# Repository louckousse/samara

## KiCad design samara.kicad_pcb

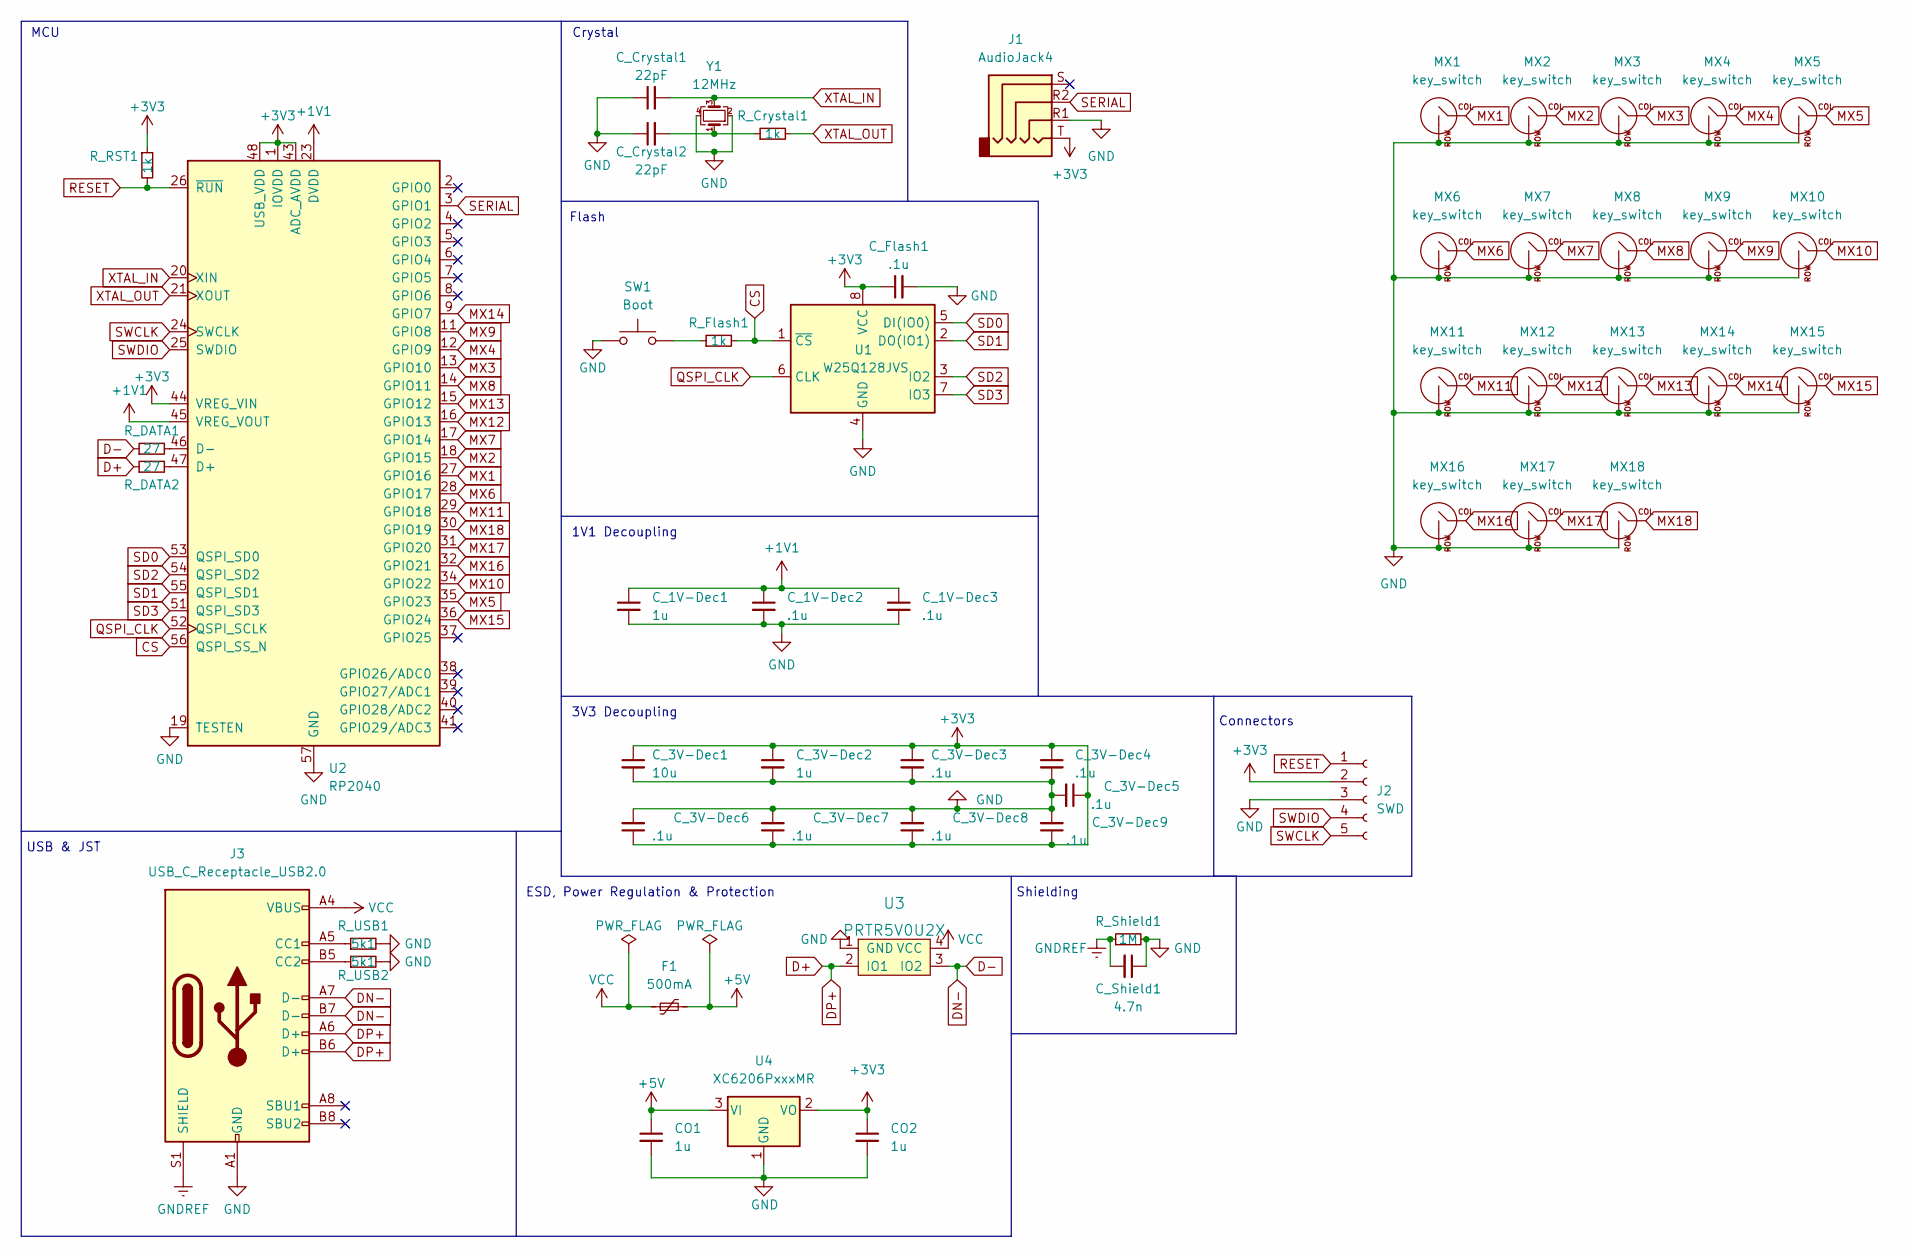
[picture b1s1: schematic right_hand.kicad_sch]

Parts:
CO1, CO2: 1u; C_0402_1005Metric
C_1V-Dec1, C_3V-Dec2: 1u; C_0402_1005Metric
C_1V-Dec2, C_1V-Dec3, C_3V-Dec3, C_3V-Dec4, C_3V-Dec5, C_3V-Dec6, C_3V-Dec7, C_3V-Dec8, C_3V-Dec9: .1u; C_0402_1005Metric
C_3V-Dec1: 10u; C_0402_1005Metric
C_Crystal1, C_Crystal2: 22pF; C_0402_1005Metric
C_Flash1: .1u; C_0402_1005Metric
C_Shield1: 4.7n; C_0402_1005Metric
F1: 500mA; Fuse_0805_2012Metric
J1: AudioJack4; Jack_3.5mm_PJ320D_Horizontal
J2: SWD; PinHeader_1x05_P2.54mm_Vertical
J3: USB_C_Receptacle_USB2.0; HRO-TYPE-C-31-M-12-Assembly
MX1, MX2, MX3, MX4, MX5, MX6, MX7, MX8, MX9, MX10, MX11, MX12, MX13, MX14, MX15, MX16, MX17, MX18: key_switch; Kailh_socket_MX
R_Crystal1: 1k; R_0402_1005Metric
R_DATA1, R_DATA2: 27; R_0402_1005Metric
R_Flash1: 1k; R_0402_1005Metric
R_RST1: 1k; R_0402_1005Metric
R_Shield1: 1M; R_0402_1005Metric
R_USB1, R_USB2: 5k1; R_0402_1005Metric
SW1: Boot; PinHeader_1x02_P2.54mm_Vertical
U1: W25Q128JVS; SOIC-8_5.23x5.23mm_P1.27mm
U2: RP2040; RP2040-QFN-56
U3: PRTR5V0U2X; SOT-143
U4: XC6206PxxxMR; SOT-23
Y1: 12MHz; Crystal_SMD_3225-4Pin_3.2x2.5mm

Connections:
+1V1: C_1V-Dec1.1, C_1V-Dec2.1, C_1V-Dec3.1, U2.23 (DVDD), U2.45 (VREG_VOUT), U2.50 (DVDD); also elsewhere on the board
+3V3: CO2.1, C_3V-Dec1.1, C_3V-Dec2.1, C_3V-Dec3.1, C_3V-Dec4.1, C_3V-Dec5.1, C_3V-Dec6.1, C_3V-Dec7.1, C_3V-Dec8.1, C_3V-Dec9.1, C_Flash1.1, J1.T, J2.2, R_RST1.1, U1.8 (VCC), U2.1 (IOVDD), U2.10 (IOVDD), U2.22 (IOVDD), U2.33 (IOVDD), U2.42 (IOVDD), U2.43 (ADC_AVDD), U2.44 (VREG_VIN), U2.48 (USB_VDD), U2.49 (IOVDD), U4.2 (VO); also elsewhere on the board
+5V: CO1.1, F1.2, U4.3 (VI); also elsewhere on the board
CS: R_Flash1.2, U1.1 (~CS), U2.56 (QSPI_SS_N)
D+: J3.A6 (D+), J3.B6 (D+), R_DATA2.1, U3.2 (IO1)
D-: J3.A7 (D-), J3.B7 (D-), R_DATA1.1, U3.3 (IO2)
GND: CO1.2, CO2.2, C_1V-Dec1.2, C_1V-Dec2.2, C_1V-Dec3.2, C_3V-Dec1.2, C_3V-Dec2.2, C_3V-Dec3.2, C_3V-Dec4.2, C_3V-Dec5.2, C_3V-Dec6.2, C_3V-Dec7.2, C_3V-Dec8.2, C_3V-Dec9.2, C_Crystal1.1, C_Crystal2.1, C_Flash1.2, C_Shield1.1, J1.R1, J2.3, J3.A1 (GND), J3.B1 (GND), MX1.2 (ROW), MX2.2 (ROW), MX3.2 (ROW), MX4.2 (ROW), MX5.2 (ROW), MX6.2 (ROW), MX7.2 (ROW), MX8.2 (ROW), MX9.2 (ROW), MX10.2 (ROW), MX11.2 (ROW), MX12.2 (ROW), MX13.2 (ROW), MX14.2 (ROW), MX15.2 (ROW), MX16.2 (ROW), MX17.2 (ROW), MX18.2 (ROW), R_Shield1.2, R_USB1.2, R_USB2.2, SW1.1, U1.4 (GND), U2.19 (TESTEN), U2.57 (GND), U3.1 (GND), U4.1 (GND), Y1.2, Y1.4; also elsewhere on the board
GNDREF: C_Shield1.2, J3.S1 (SHIELD), R_Shield1.1; also elsewhere on the board
MX1: MX1.1 (Passive), U2.27 (GPIO16)
MX2: MX2.1 (Passive), U2.18 (GPIO15)
MX3: MX3.1 (Passive), U2.13 (GPIO10)
MX4: MX4.1 (Passive), U2.12 (GPIO9)
MX5: MX5.1 (Passive), U2.35 (GPIO23)
MX6: MX6.1 (Passive), U2.28 (GPIO17)
MX7: MX7.1 (Passive), U2.17 (GPIO14)
MX8: MX8.1 (Passive), U2.14 (GPIO11)
MX9: MX9.1 (Passive), U2.11 (GPIO8)
MX10: MX10.1 (Passive), U2.34 (GPIO22)
MX11: MX11.1 (Passive), U2.29 (GPIO18)
MX12: MX12.1 (Passive), U2.16 (GPIO13)
MX13: MX13.1 (Passive), U2.15 (GPIO12)
MX14: MX14.1 (Passive), U2.9 (GPIO7)
MX15: MX15.1 (Passive), U2.36 (GPIO24)
MX16: MX16.1 (Passive), U2.32 (GPIO21)
MX17: MX17.1 (Passive), U2.31 (GPIO20)
MX18: MX18.1 (Passive), U2.30 (GPIO19)
unnamed: C_Crystal2.2, R_Crystal1.1, Y1.1
unnamed: J3.A5 (CC1), R_USB1.1
unnamed: J3.B5 (CC2), R_USB2.1
unnamed: R_Flash1.1, SW1.2
unnamed: R_DATA2.2, U2.47 (D+)
unnamed: R_DATA1.2, U2.46 (D-)
QSPI_CLK: U1.6 (CLK), U2.52 (QSPI_SCLK)
RESET: J2.1, R_RST1.2, U2.26 (~RUN)
SD0: U1.5 (DI(IO0)), U2.53 (QSPI_SD0)
SD1: U1.2 (DO(IO1)), U2.55 (QSPI_SD1)
SD2: U1.3 (IO2), U2.54 (QSPI_SD2)
SD3: U1.7 (IO3), U2.51 (QSPI_SD3)
SERIAL: J1.R2, U2.3 (GPIO1)
SWCLK: J2.5, U2.24 (SWCLK)
SWDIO: J2.4, U2.25 (SWDIO)
VCC: F1.1, J3.A4 (VBUS), J3.B4 (VBUS), U3.4 (VCC); also elsewhere on the board
XTAL_IN: C_Crystal1.2, U2.20 (XIN), Y1.3
XTAL_OUT: R_Crystal1.2, U2.21 (XOUT)

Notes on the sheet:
USB & JST
MCU
Connectors
3V3 Decoupling
ESD, Power Regulation & Protection
Shielding
Flash
Crystal
1V1 Decoupling

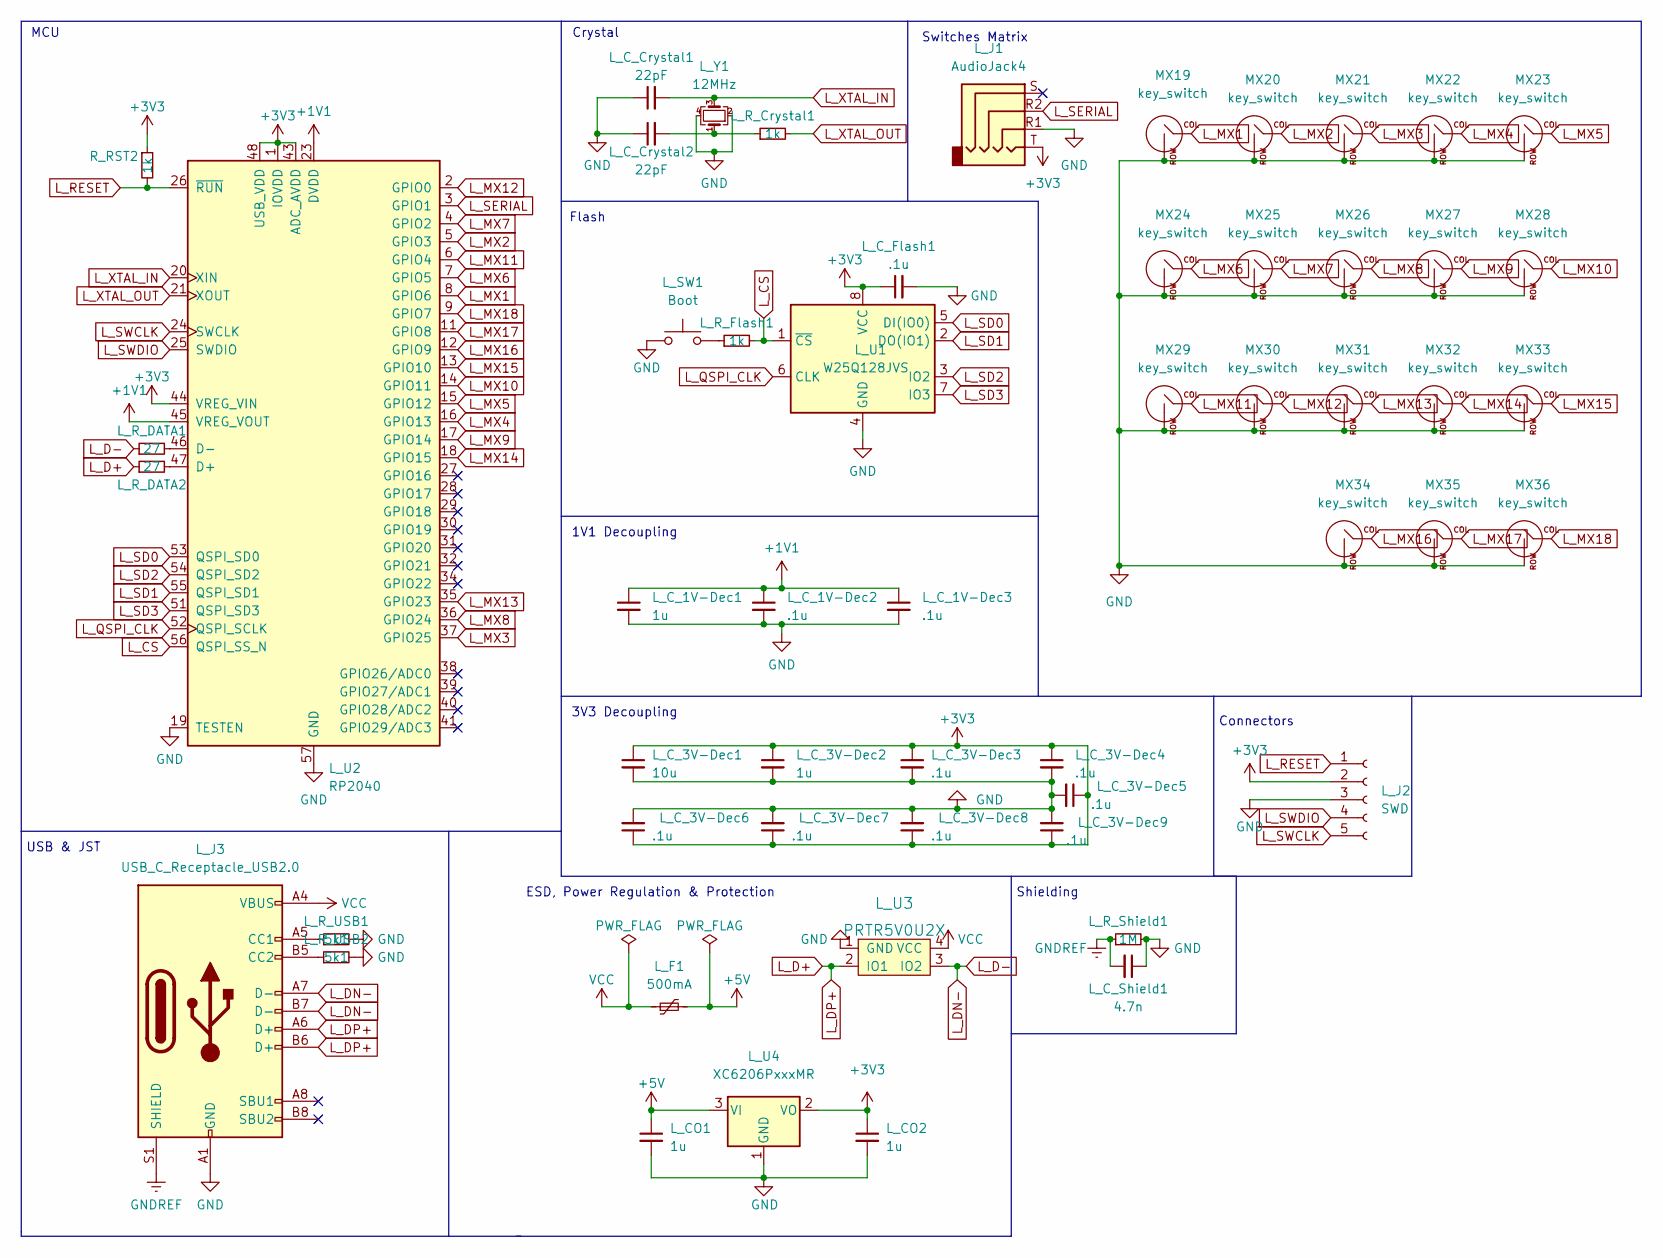
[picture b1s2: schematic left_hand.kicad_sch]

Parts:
L_CO1, L_CO2: 1u; C_0402_1005Metric
L_C_1V-Dec1, L_C_3V-Dec2: 1u; C_0402_1005Metric
L_C_1V-Dec2, L_C_1V-Dec3, L_C_3V-Dec3, L_C_3V-Dec4, L_C_3V-Dec5, L_C_3V-Dec6, L_C_3V-Dec7, L_C_3V-Dec8, L_C_3V-Dec9: .1u; C_0402_1005Metric
L_C_3V-Dec1: 10u; C_0402_1005Metric
L_C_Crystal1, L_C_Crystal2: 22pF; C_0402_1005Metric
L_C_Flash1: .1u; C_0402_1005Metric
L_C_Shield1: 4.7n; C_0402_1005Metric
L_F1: 500mA; Fuse_0805_2012Metric
L_J1: AudioJack4; Jack_3.5mm_PJ320D_Horizontal
L_J2: SWD; PinHeader_1x05_P2.54mm_Vertical
L_J3: USB_C_Receptacle_USB2.0; HRO-TYPE-C-31-M-12-Assembly
L_R_Crystal1: 1k; R_0402_1005Metric
L_R_DATA1, L_R_DATA2: 27; R_0402_1005Metric
L_R_Flash1: 1k; R_0402_1005Metric
L_R_Shield1: 1M; R_0402_1005Metric
L_R_USB1, L_R_USB2: 5k1; R_0402_1005Metric
L_SW1: Boot; PinHeader_1x02_P2.54mm_Vertical
L_U1: W25Q128JVS; SOIC-8_5.23x5.23mm_P1.27mm
L_U2: RP2040; RP2040-QFN-56
L_U3: PRTR5V0U2X; SOT-143
L_U4: XC6206PxxxMR; SOT-23
L_Y1: 12MHz; Crystal_SMD_3225-4Pin_3.2x2.5mm
MX19, MX20, MX21, MX22, MX23, MX24, MX25, MX26, MX27, MX28, MX29, MX30, MX31, MX32, MX33, MX34, MX35, MX36: key_switch; Kailh_socket_MX
R_RST2: 1k; R_0402_1005Metric

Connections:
+1V1: L_C_1V-Dec1.1, L_C_1V-Dec2.1, L_C_1V-Dec3.1, L_U2.23 (DVDD), L_U2.45 (VREG_VOUT), L_U2.50 (DVDD); also elsewhere on the board
+3V3: L_CO2.1, L_C_3V-Dec1.1, L_C_3V-Dec2.1, L_C_3V-Dec3.1, L_C_3V-Dec4.1, L_C_3V-Dec5.1, L_C_3V-Dec6.1, L_C_3V-Dec7.1, L_C_3V-Dec8.1, L_C_3V-Dec9.1, L_C_Flash1.1, L_J1.T, L_J2.2, L_U1.8 (VCC), L_U2.1 (IOVDD), L_U2.10 (IOVDD), L_U2.22 (IOVDD), L_U2.33 (IOVDD), L_U2.42 (IOVDD), L_U2.43 (ADC_AVDD), L_U2.44 (VREG_VIN), L_U2.48 (USB_VDD), L_U2.49 (IOVDD), L_U4.2 (VO), R_RST2.1; also elsewhere on the board
+5V: L_CO1.1, L_F1.2, L_U4.3 (VI); also elsewhere on the board
GND: L_CO1.2, L_CO2.2, L_C_1V-Dec1.2, L_C_1V-Dec2.2, L_C_1V-Dec3.2, L_C_3V-Dec1.2, L_C_3V-Dec2.2, L_C_3V-Dec3.2, L_C_3V-Dec4.2, L_C_3V-Dec5.2, L_C_3V-Dec6.2, L_C_3V-Dec7.2, L_C_3V-Dec8.2, L_C_3V-Dec9.2, L_C_Crystal1.1, L_C_Crystal2.1, L_C_Flash1.2, L_C_Shield1.1, L_J1.R1, L_J2.3, L_J3.A1 (GND), L_J3.B1 (GND), L_R_Shield1.2, L_R_USB1.2, L_R_USB2.2, L_SW1.1, L_U1.4 (GND), L_U2.19 (TESTEN), L_U2.57 (GND), L_U3.1 (GND), L_U4.1 (GND), L_Y1.2, L_Y1.4, MX19.2 (ROW), MX20.2 (ROW), MX21.2 (ROW), MX22.2 (ROW), MX23.2 (ROW), MX24.2 (ROW), MX25.2 (ROW), MX26.2 (ROW), MX27.2 (ROW), MX28.2 (ROW), MX29.2 (ROW), MX30.2 (ROW), MX31.2 (ROW), MX32.2 (ROW), MX33.2 (ROW), MX34.2 (ROW), MX35.2 (ROW), MX36.2 (ROW); also elsewhere on the board
GNDREF: L_C_Shield1.2, L_J3.S1 (SHIELD), L_R_Shield1.1; also elsewhere on the board
L_CS: L_R_Flash1.2, L_U1.1 (~CS), L_U2.56 (QSPI_SS_N)
L_D+: L_J3.A6 (D+), L_J3.B6 (D+), L_R_DATA2.1, L_U3.2 (IO1)
L_D-: L_J3.A7 (D-), L_J3.B7 (D-), L_R_DATA1.1, L_U3.3 (IO2)
L_MX1: L_U2.8 (GPIO6), MX19.1 (Passive)
L_MX2: L_U2.5 (GPIO3), MX20.1 (Passive)
L_MX3: L_U2.37 (GPIO25), MX21.1 (Passive)
L_MX4: L_U2.16 (GPIO13), MX22.1 (Passive)
L_MX5: L_U2.15 (GPIO12), MX23.1 (Passive)
L_MX6: L_U2.7 (GPIO5), MX24.1 (Passive)
L_MX7: L_U2.4 (GPIO2), MX25.1 (Passive)
L_MX8: L_U2.36 (GPIO24), MX26.1 (Passive)
L_MX9: L_U2.17 (GPIO14), MX27.1 (Passive)
L_MX10: L_U2.14 (GPIO11), MX28.1 (Passive)
L_MX11: L_U2.6 (GPIO4), MX29.1 (Passive)
L_MX12: L_U2.2 (GPIO0), MX30.1 (Passive)
L_MX13: L_U2.35 (GPIO23), MX31.1 (Passive)
L_MX14: L_U2.18 (GPIO15), MX32.1 (Passive)
L_MX15: L_U2.13 (GPIO10), MX33.1 (Passive)
L_MX16: L_U2.12 (GPIO9), MX34.1 (Passive)
L_MX17: L_U2.11 (GPIO8), MX35.1 (Passive)
L_MX18: L_U2.9 (GPIO7), MX36.1 (Passive)
L_QSPI_CLK: L_U1.6 (CLK), L_U2.52 (QSPI_SCLK)
L_RESET: L_J2.1, L_U2.26 (~RUN), R_RST2.2
L_SD0: L_U1.5 (DI(IO0)), L_U2.53 (QSPI_SD0)
L_SD1: L_U1.2 (DO(IO1)), L_U2.55 (QSPI_SD1)
L_SD2: L_U1.3 (IO2), L_U2.54 (QSPI_SD2)
L_SD3: L_U1.7 (IO3), L_U2.51 (QSPI_SD3)
L_SERIAL: L_J1.R2, L_U2.3 (GPIO1)
L_SWCLK: L_J2.5, L_U2.24 (SWCLK)
L_SWDIO: L_J2.4, L_U2.25 (SWDIO)
L_XTAL_IN: L_C_Crystal1.2, L_U2.20 (XIN), L_Y1.3
L_XTAL_OUT: L_R_Crystal1.2, L_U2.21 (XOUT)
unnamed: L_C_Crystal2.2, L_R_Crystal1.1, L_Y1.1
unnamed: L_J3.A5 (CC1), L_R_USB1.1
unnamed: L_J3.B5 (CC2), L_R_USB2.1
unnamed: L_R_Flash1.1, L_SW1.2
unnamed: L_R_DATA2.2, L_U2.47 (D+)
unnamed: L_R_DATA1.2, L_U2.46 (D-)
VCC: L_F1.1, L_J3.A4 (VBUS), L_J3.B4 (VBUS), L_U3.4 (VCC); also elsewhere on the board

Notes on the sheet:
Connectors
USB & JST
Crystal
MCU
1V1 Decoupling
Flash
ESD, Power Regulation & Protection
Shielding
Switches Matrix
3V3 Decoupling

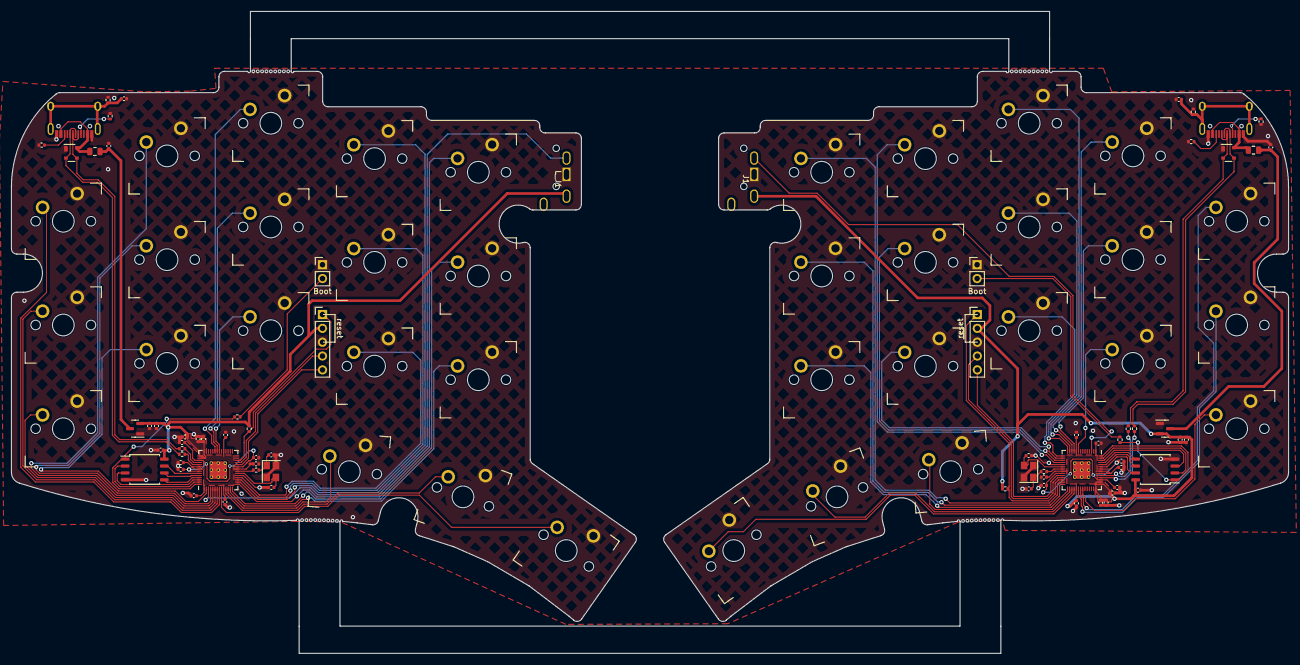
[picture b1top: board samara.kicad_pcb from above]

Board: 2 copper layers, 234.5 x 117.9 mm, 108 parts (0 on the bottom side), 82 nets.

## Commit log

2023-04-20 alpha
2023-06-26 final, working
2023-08-15 replace trrs
2024-10-19 hotwap prod
2024-10-19 add plate.dxf
2024-10-19 update lib
